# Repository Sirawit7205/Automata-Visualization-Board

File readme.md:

# CMOS Elementary Automata Visualization Board

This is an  open-source KiCad design files for a circuit that could generate and visualize [Elementary Automata](https://mathworld.wolfram.com/ElementaryCellularAutomaton.html) only by using common logic ICs. There are two versions available: Standard and Minimal. 

## Standard Version

Standard version is a large board of size 247x127mm (9.7x5in), suitable for putting in a frame. Featuring:

 - 26 Logic ICs in DIP package. (Okay, I have an ATMEGA328 here but it's here just to drive the display. Its firmware is available here as well.)
 - 1.44 inch TFT display with a display driver which can draws a complete picture of that elementary automata rule.
 - Fully visualized 65-bit shift register so you can see how the data flows.
 - Fully selectable 8-bit automata rule input.
 - An LSFR pseudo-random rules generator.
 - Status display.
 - Drawing speed adjustment.
 - All through hole design. Should be relatively easy to solder.

We are currently at Revision 3. Changelog is below:

**Revision 3 (July 2020)**
 - Fixed all of the issues found in rev 2.
 - BOMs consolidated to lessen the unique parts count.
 - New LFSR circuit, the rare CD4006 is no longer required.
 - Updated all footprints to the latest version.
 - Minor changes to the appearances of the PCB.

**Revision 2 (May 2020)**
 - Fixed Connector orientation for the display and the DIP switch.
 - Connected GND to mounting holes
 - Change of parts in the power section due to sourcing issue.
 
**Revision 1 (January 2020)**
 - Initial Design

## Minimal Version

Minimal Version is a smaller board of size 129x72mm (5x3in). It is suitable for carrying around to show off. Featuring:

 - 23 Logic ICs in SOT, SOIC, TSSOP, and TQFP packages.
 - 1.44 inch TFT display.
 - Fully selectable 8-bit automata rule input.
 - An LSFR pseudo-random rules generator.
 - Status display.
 - Drawing speed adjustment.
 - Very challenging SMD soldering practice kit.
 - The PCB should be much cheaper to produce. It's still a little bit too large to fit in 10x10cm requirements for many cheap PCB fabs though, I might try to squeeze it down later.

We are currently at Revision 3. Changelog is below:

**Revision 3 (July 2020)**
 - Fixed all of the issues found in smd rev 2.
 - BOMs consolidated to lessen the unique parts count.
 - New LFSR circuit, the rare CD4006 is no longer required.
 - Updated all footprints to the latest version.
 - Minor changes to the appearances of the PCB.

**Revision 2 (May 2020)**
 - Fixed all of the issues found in rev 1 of the Standard version.
 - Change of parts in the power section due to sourcing issue.
 
**Revision 1 (April 2020)**
 - Initial Design (Based on Standard version)

## What is provided
The goal of this repository is to enable you to build this on your own as easy as possible (although I originally plan to sell this as a kit as well). **I've included all of the schematics, gerbers, BOMs, and display driver firmware for you to use.** And this work is licensed under a [Creative Commons Attribution-NonCommercial 4.0 International License](http://creativecommons.org/licenses/by-nc/4.0/).

Unfortunately. I have to excluded the 3D models use to render the board in KiCAD because I don't know how each of them was licensed. They are all from GrabCad and you could search and download them by yourself.

**Note: Due to this, there might be a popup warning you about "3D model Search Path" in PCBNew. I honestly don't know how to fix this but it will not affect any KiCAD functionality.**

## Credits
 - DIP switch model by austfox: https://grabcad.com/library/dip-switches-1
 - 1.44inch LCD model by John: https://grabcad.com/library/1-44in-lcd-tft-1
 - Sliding switch model by Jonn: https://grabcad.com/library/selector-switch-assortment-1
 - Trimpot model by Markus Walter: https://grabcad.com/library/bourns-3362p-1-102lf
 - DIP ICs in socket models by Dirk Wouters: https://grabcad.com/library/ic-dip-packages-with-sockets-in-pitch-7-62mm-1
 - TO-220 package model by Egor Chugay: https://grabcad.com/library/to-220-transistor-package-1
 - DC Power Jack model by J. F. Gomez: https://grabcad.com/library/dc-power-jack-5-5mm-x-2-1mm-2-54mm-pitch-1
 - SMD 5032 Crystal 2-Pin model by Dirk Wouters: https://grabcad.com/library/smd-5032-crystal-2-pin-1
 - LED Bar Graph model by austfox: https://grabcad.com/library/led-bar-graph-2
 - 3306P1102, 3362P_1, NE555DR, OS102011MA1QN1, TO229P239X654X978-3P footprint symbols by SamacSys

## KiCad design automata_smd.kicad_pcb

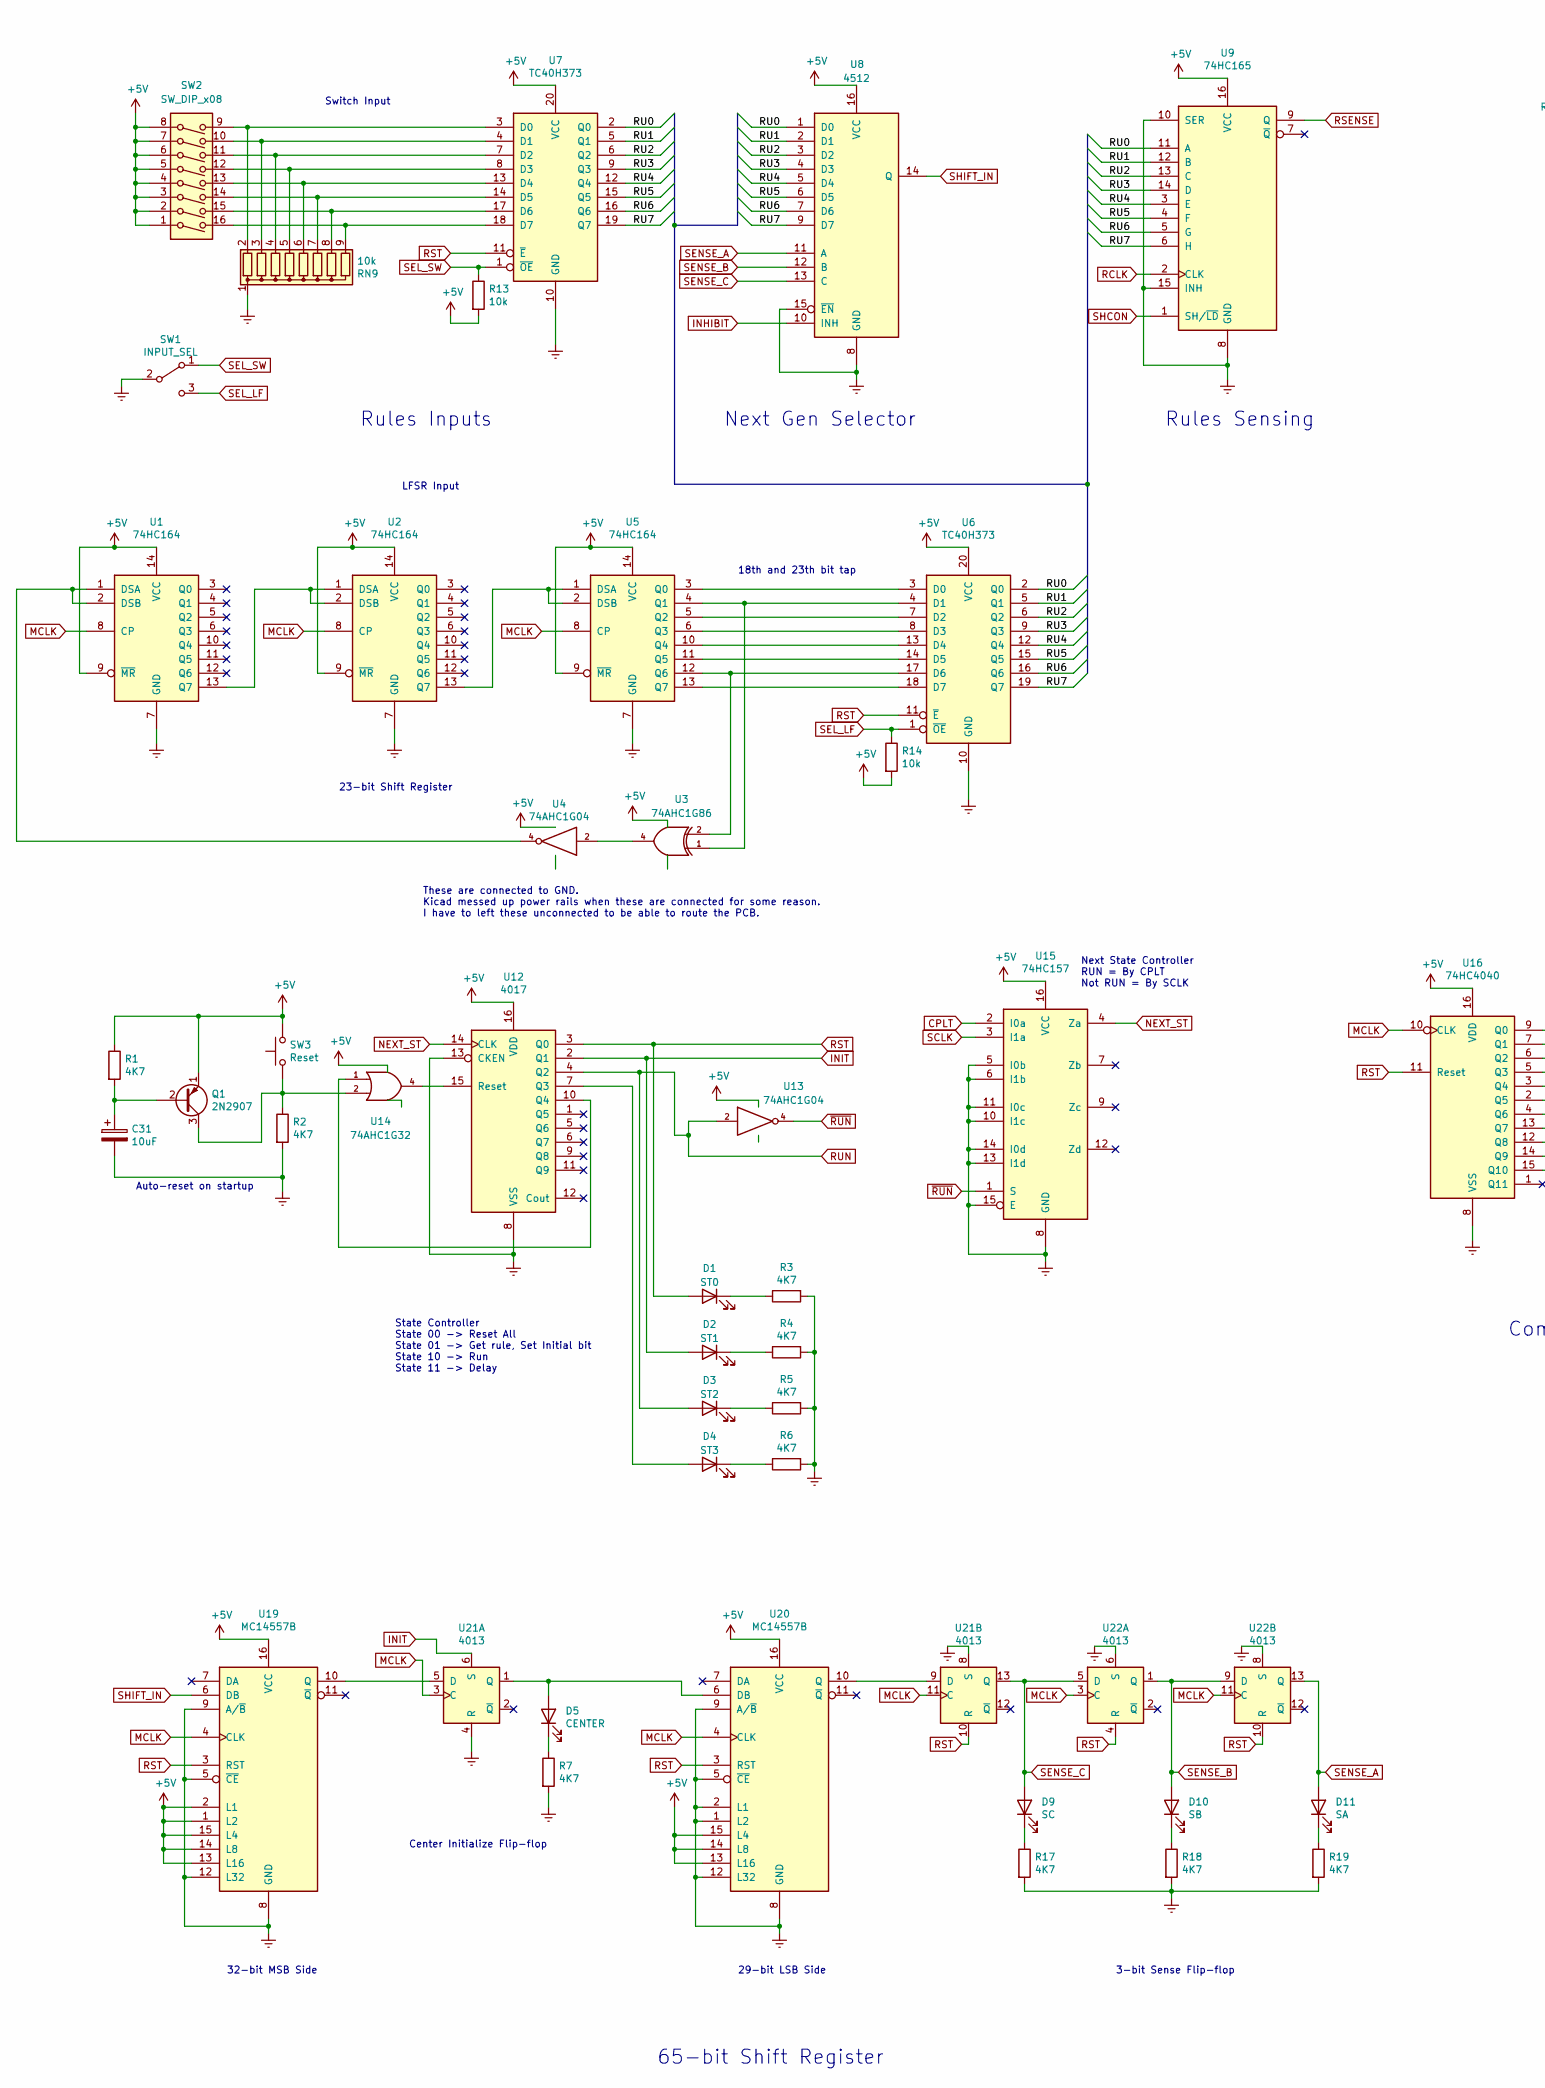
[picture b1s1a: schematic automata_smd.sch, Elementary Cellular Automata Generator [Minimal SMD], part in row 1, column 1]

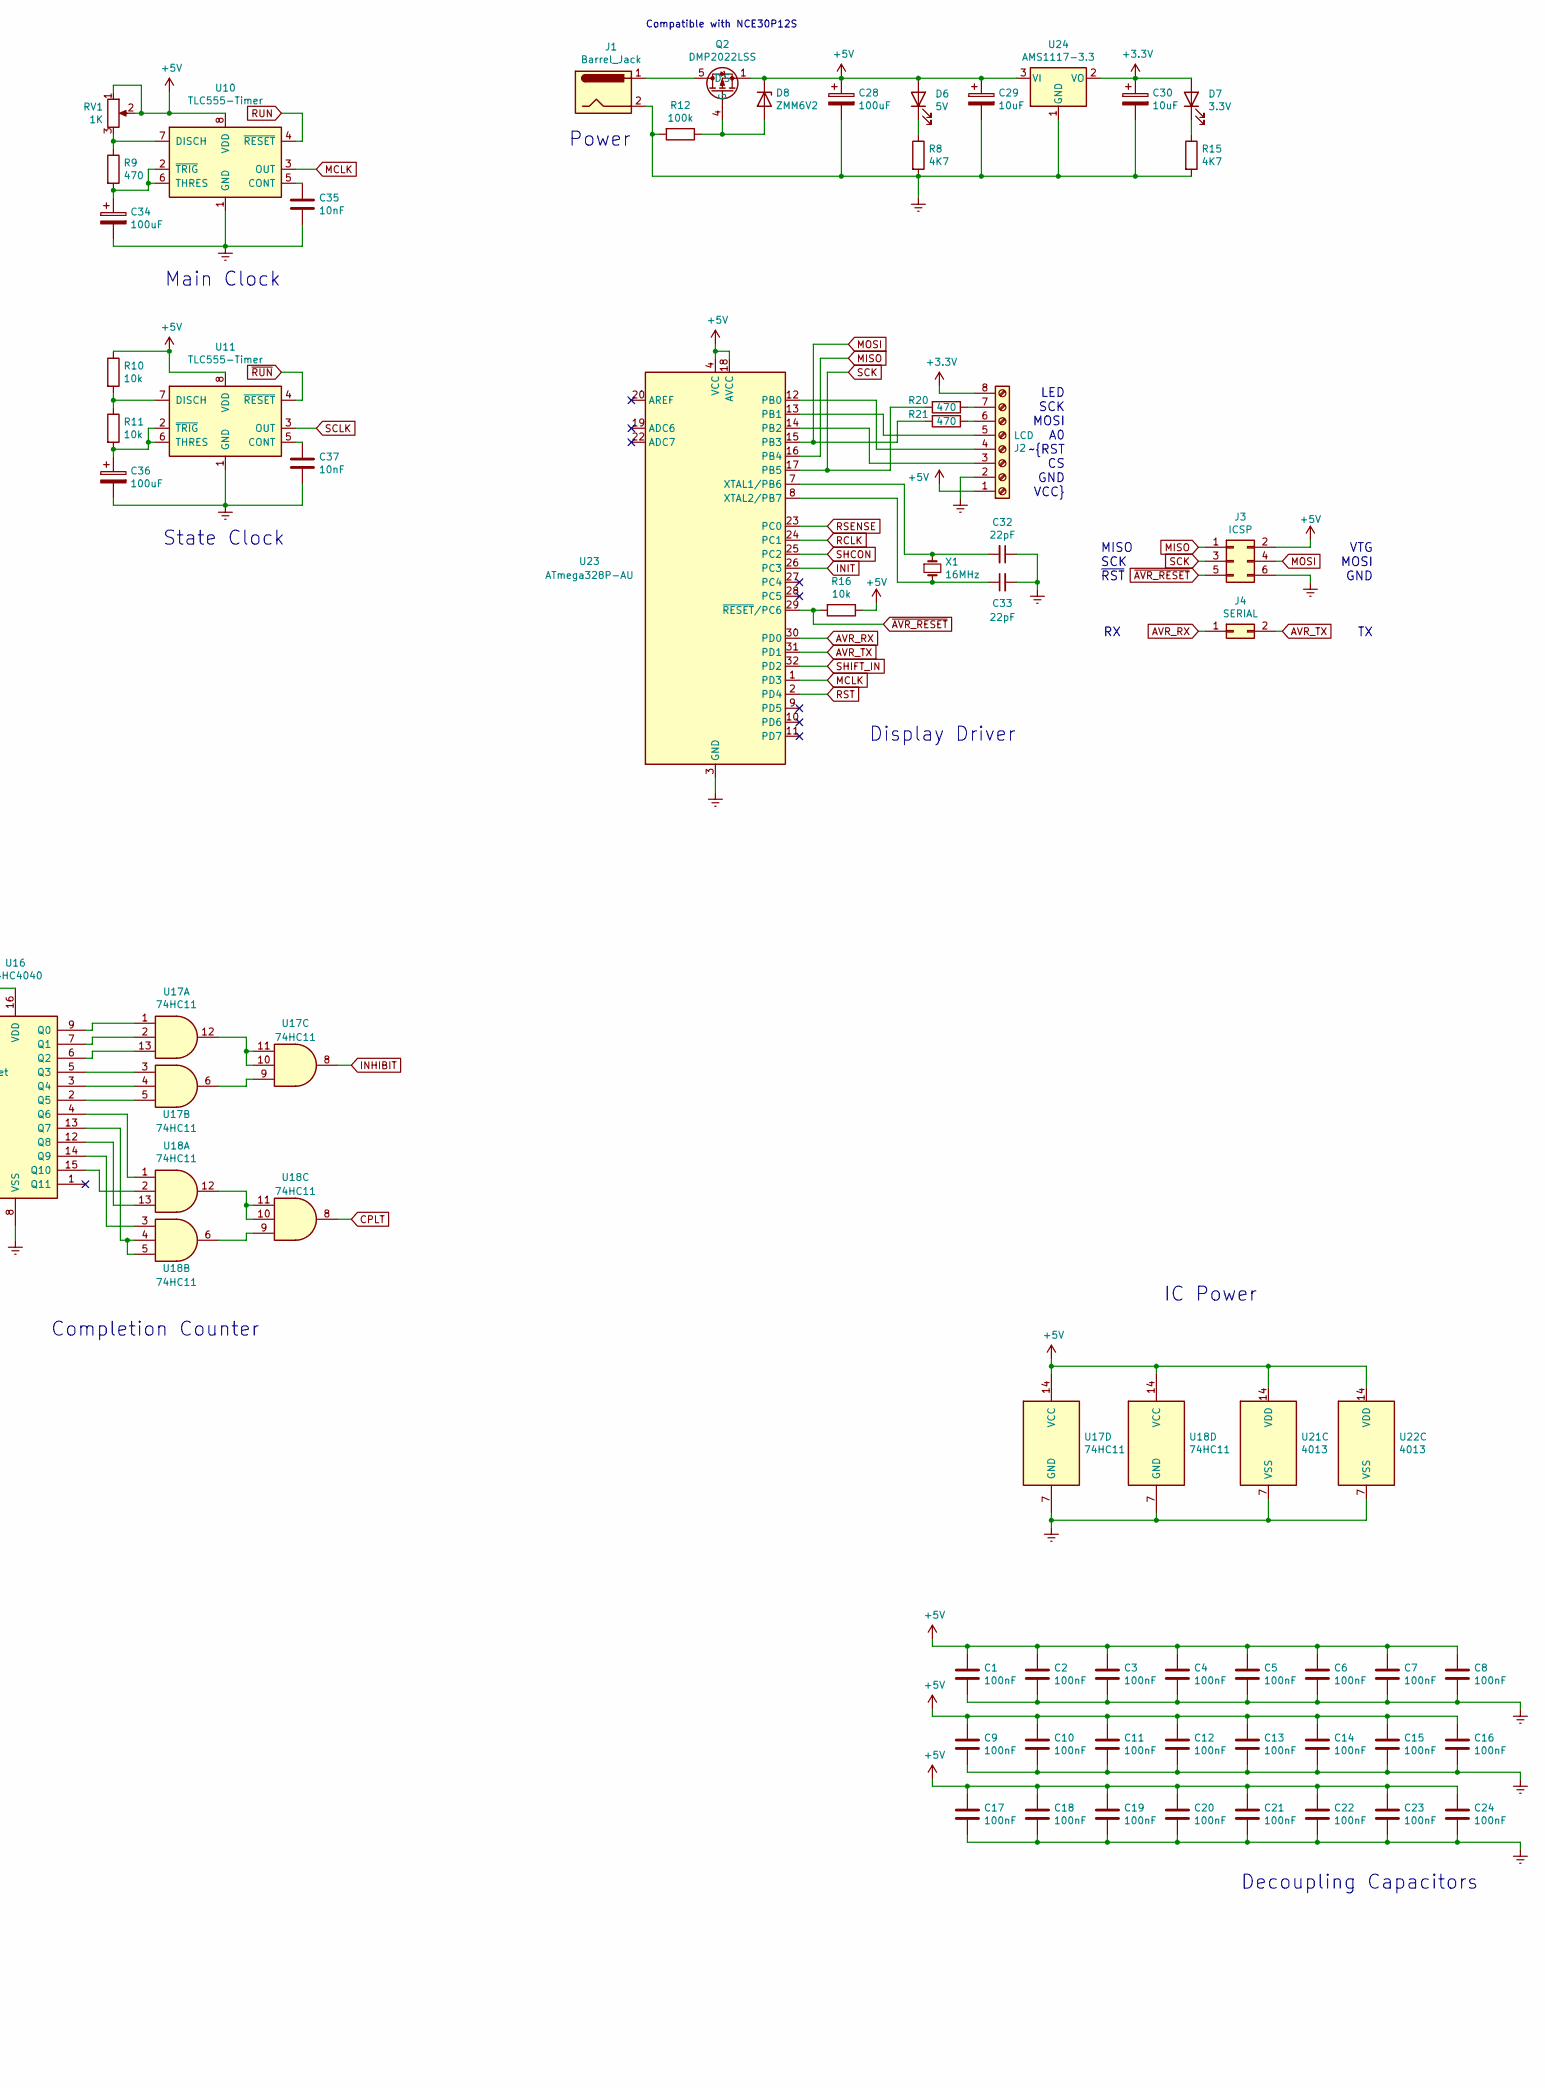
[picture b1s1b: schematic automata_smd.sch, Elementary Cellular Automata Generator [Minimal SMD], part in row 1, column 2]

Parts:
C1: 100nF; TSSOP-14_4.4x5mm_P0.65mm
C2, C3, C4, C5, C6, C7, C8, C9, C10, C11, C12, C13, C14, C15, C16, C17, C18, C19, C20, C21, C22, C23, C24: 100nF; C_0603_1608Metric
C28, C34, C36: 100uF; CP_Radial_D8.0mm_P2.50mm
C29, C30, C31: 10uF; CP_Radial_D5.0mm_P2.00mm
C32, C33: 22pF; C_0603_1608Metric
C35, C37: 10nF; C_0603_1608Metric
D1: ST0; LED_0603_1608Metric
D2: ST1; LED_0603_1608Metric
D3: ST2; LED_0603_1608Metric
D4: ST3; LED_0603_1608Metric
D5: CENTER; LED_0603_1608Metric
D6: 5V; LED_0603_1608Metric
D7: 3.3V; LED_0603_1608Metric
D8: ZMM6V2; D_MiniMELF
D9: SC; LED_0603_1608Metric
D10: SB; LED_0603_1608Metric
D11: SA; LED_0603_1608Metric
J1: Barrel_Jack; BarrelJack_Horizontal
J2: LCD; PinHeader_1x08_P2.54mm_Vertical
J3: ICSP; PinHeader_2x03_P2.54mm_Vertical
J4: SERIAL; PinHeader_2x01_P2.54mm_Vertical
Q1: 2N2907; SOT-23
Q2: DMP2022LSS; SO-8_3.9x4.9mm_P1.27mm
R1, R2, R3, R4, R5, R6, R7, R8, R15, R17, R18, R19: 4K7; R_0603_1608Metric
R9, R20, R21: 470; R_0603_1608Metric
R10, R11, R13, R14, R16: 10k; R_0603_1608Metric
R12: 100k; R_0603_1608Metric
RN9: 10k; R_Array_SIP9
RV1: 1K; 3362P_1
SW1: INPUT_SEL; OS102011MA1QN1
SW2: SW_DIP_x08; SW_DIP_SPSTx08_Slide_9.78x22.5mm_W7.62mm_P2.54mm
SW3: Reset; SW_PUSH_6mm
U1, U2, U5: 74HC164; TSSOP-14_4.4x5mm_P0.65mm
U3: 74AHC1G86; SOT-23-5
U4, U13: 74AHC1G04; SOT-23-5
U6, U7: TC40H373; TSSOP-20_4.4x6.5mm_P0.65mm
U8: 4512; TSSOP-16_4.4x5mm_P0.65mm
U9: 74HC165; TSSOP-16_4.4x5mm_P0.65mm
U10, U11: TLC555-Timer; SOIC-8_3.9x4.9mm_P1.27mm
U12: 4017; TSSOP-16_4.4x5mm_P0.65mm
U14: 74AHC1G32; SOT-23-5
U15: 74HC157; TSSOP-16_4.4x5mm_P0.65mm
U16: 74HC4040; TSSOP-16_4.4x5mm_P0.65mm
U17, U18: 74HC11; TSSOP-14_4.4x5mm_P0.65mm
U19, U20: MC14557B; SOIC-16W_7.5x10.3mm_P1.27mm
U21, U22: 4013; TSSOP-14_4.4x5mm_P0.65mm
U23: ATmega328P-AU; TQFP-32_7x7mm_P0.8mm
U24: AMS1117-3.3; SOT-223-3_TabPin2
X1: 16MHz; Crystal_SMD_5032-2Pin_5.0x3.2mm

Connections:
+3V3: C30.1, D7.2 (A), J2.8, U24.2 (VO)
/RU0: U6.2 (Q0), U7.2 (Q0), U8.1 (D0), U9.11 (A)
/RU1: U6.5 (Q1), U7.5 (Q1), U8.2 (D1), U9.12 (B)
/RU2: U6.6 (Q2), U7.6 (Q2), U8.3 (D2), U9.13 (C)
/RU3: U6.9 (Q3), U7.9 (Q3), U8.4 (D3), U9.14 (D)
/RU4: U6.12 (Q4), U7.12 (Q4), U8.5 (D4), U9.3 (E)
/RU5: U6.15 (Q5), U7.15 (Q5), U8.6 (D5), U9.4 (F)
/RU6: U6.16 (Q6), U7.16 (Q6), U8.7 (D6), U9.5 (G)
/RU7: U6.19 (Q7), U7.19 (Q7), U8.9 (D7), U9.6 (H)
AVR_RX: J4.1, U23.30 (PD0)
AVR_TX: J4.2, U23.31 (PD1)
CPLT: U15.2 (I0a), U18.8
INHIBIT: U8.10 (INH), U17.8
INIT: D2.2 (A), U12.2 (Q1), U21.6 (S), U23.26 (PC3)
MCLK: U1.8 (CP), U2.8 (CP), U5.8 (CP), U10.3 (OUT), U16.10 (CLK), U19.4 (CLK), U20.4 (CLK), U21.3 (C), U21.11 (C), U22.3 (C), U22.11 (C), U23.1 (PD3)
MISO: J3.1, U23.16 (PB4)
MOSI: J3.4, R21.2, U23.15 (PB3)
NEXT_ST: U12.14 (CLK), U15.4 (Za)
unnamed: C31.1, Q1.2 (B), R1.2
unnamed: C32.2, U23.7 (XTAL1/PB6), X1.1
unnamed: C33.1, U23.8 (XTAL2/PB7), X1.2
unnamed: C34.1, R9.2, U10.2 (~TRIG), U10.6 (THRES)
unnamed: C35.1, U10.5 (CONT)
unnamed: C36.1, R11.2, U11.2 (~TRIG), U11.6 (THRES)
unnamed: C37.1, U11.5 (CONT)
unnamed: D1.1 (K), R3.1
unnamed: D2.1 (K), R4.1
unnamed: D3.1 (K), R5.1
unnamed: D4.1 (K), R6.1
unnamed: D4.2 (A), U12.7 (Q3)
unnamed: D5.1 (K), R7.1
unnamed: D5.2 (A), U20.6 (DB), U21.1 (Q)
unnamed: D6.1 (K), R8.1
unnamed: D7.1 (K), R15.1
unnamed: D8.2 (A), Q2.4 (G), R12.1
unnamed: D9.1 (K), R17.1
unnamed: D10.1 (K), R18.1
unnamed: D11.1 (K), R19.1
unnamed: J1.1, Q2.5 (D), Q2.6 (D), Q2.7 (D), Q2.8 (D)
unnamed: J2.3, U23.14 (PB2)
unnamed: J2.4, U23.12 (PB0)
unnamed: J2.5, U23.13 (PB1)
unnamed: J2.6, R21.1
unnamed: J2.7, R20.1
unnamed: Q1.3 (C), R2.1, SW3.1, U14.2
unnamed: R9.1, RV1.3, U10.7 (DISCH)
unnamed: R10.2, R11.1, U11.7 (DISCH)
unnamed: RN9.2 (R1), SW2.9, U7.3 (D0)
unnamed: RN9.3 (R2), SW2.10, U7.4 (D1)
unnamed: RN9.4 (R3), SW2.11, U7.7 (D2)
unnamed: RN9.5 (R4), SW2.12, U7.8 (D3)
unnamed: RN9.6 (R5), SW2.13, U7.13 (D4)
unnamed: RN9.7 (R6), SW2.14, U7.14 (D5)
unnamed: RN9.8 (R7), SW2.15, U7.17 (D6)
unnamed: RN9.9 (R8), SW2.16, U7.18 (D7)
unnamed: U1.1 (DSA), U1.2 (DSB), U4.4
unnamed: U1.13 (Q7), U2.1 (DSA), U2.2 (DSB)
unnamed: U2.13 (Q7), U5.1 (DSA), U5.2 (DSB)
unnamed: U3.1, U5.4 (Q1), U6.4 (D1)
unnamed: U3.2, U5.12 (Q6), U6.17 (D6)
unnamed: U3.4, U4.2
unnamed: U5.3 (Q0), U6.3 (D0)
unnamed: U5.5 (Q2), U6.7 (D2)
unnamed: U5.6 (Q3), U6.8 (D3)
unnamed: U5.10 (Q4), U6.13 (D4)
unnamed: U5.11 (Q5), U6.14 (D5)
unnamed: U5.13 (Q7), U6.18 (D7)
unnamed: U12.10 (Q4), U14.1
unnamed: U12.15 (Reset), U14.4
unnamed: U16.2 (Q5), U17.5
unnamed: U16.3 (Q4), U17.4
unnamed: U16.4 (Q6), U18.1
unnamed: U16.5 (Q3), U17.3
unnamed: U16.6 (Q2), U17.13
unnamed: U16.7 (Q1), U17.2
unnamed: U16.9 (Q0), U17.1
unnamed: U16.12 (Q8), U18.13
unnamed: U16.13 (Q7), U18.4, U18.5
unnamed: U16.14 (Q9), U18.3
unnamed: U16.15 (Q10), U18.2
unnamed: U17.6, U17.9
unnamed: U17.10, U17.11, U17.12
unnamed: U18.6, U18.9
unnamed: U18.10, U18.11, U18.12
unnamed: U19.10 (Q), U21.5 (D)
unnamed: U20.10 (Q), U21.9 (D)
RCLK: U9.2 (CLK), U23.24 (PC1)
RSENSE: U9.9 (Q), U23.23 (PC0)
RST: D1.2 (A), U6.11 (~E), U7.11 (~E), U12.3 (Q0), U16.11 (Reset), U19.3 (RST), U20.3 (RST), U21.10 (R), U22.4 (R), U22.10 (R), U23.2 (PD4)
RUN: D3.2 (A), U10.4 (~RESET), U12.4 (Q2), U13.2
SCK: J3.3, R20.2, U23.17 (PB5)
SCLK: U11.3 (OUT), U15.3 (I1a)
SEL_LF: R14.1, SW1.3 (C), U6.1 (~OE)
SEL_SW: R13.1, SW1.1 (A), U7.1 (~OE)
SENSE_A: D11.2 (A), U8.11 (A), U22.13 (Q)
SENSE_B: D10.2 (A), U8.12 (B), U22.1 (Q), U22.9 (D)
SENSE_C: D9.2 (A), U8.13 (C), U21.13 (Q), U22.5 (D)
SHCON: U9.1 (SH/~LD), U23.25 (PC2)
SHIFT_IN: U8.14 (Q), U19.6 (DB), U23.32 (PD2)
~AVR_RESET: J3.5, R16.2, U23.29 (~RESET~/PC6)
~RUN: U11.4 (~RESET), U13.4, U15.1 (S)

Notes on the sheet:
Switch Input
Rules Inputs
Next Gen Selector
Completion Counter
LED SCK MOSI A0 ~RST CS GND VCC
Power
Display Driver
Rules Sensing
State Controller State 00 -> Reset All State 01 -> Get rule, Set Initial bit State 10 -> Run State 11 -> Delay
Auto-reset on startup
State Clock
Next State Controller RUN = By CPLT Not RUN = By SCLK
65-bit Shift Register
Center Initialize Flip-flop
Main Clock
Decoupling Capacitors
IC Power
32-bit MSB Side
29-bit LSB Side
3-bit Sense Flip-flop
MISO SCK ~RST
VTG MOSI GND
Compatible with NCE30P12S
LFSR Input
23-bit Shift Register
18th and 23th bit tap
These are connected to GND. Kicad messed up power rails when these are connected for some reason. I have to left these unconnected to be able to route the PCB.

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
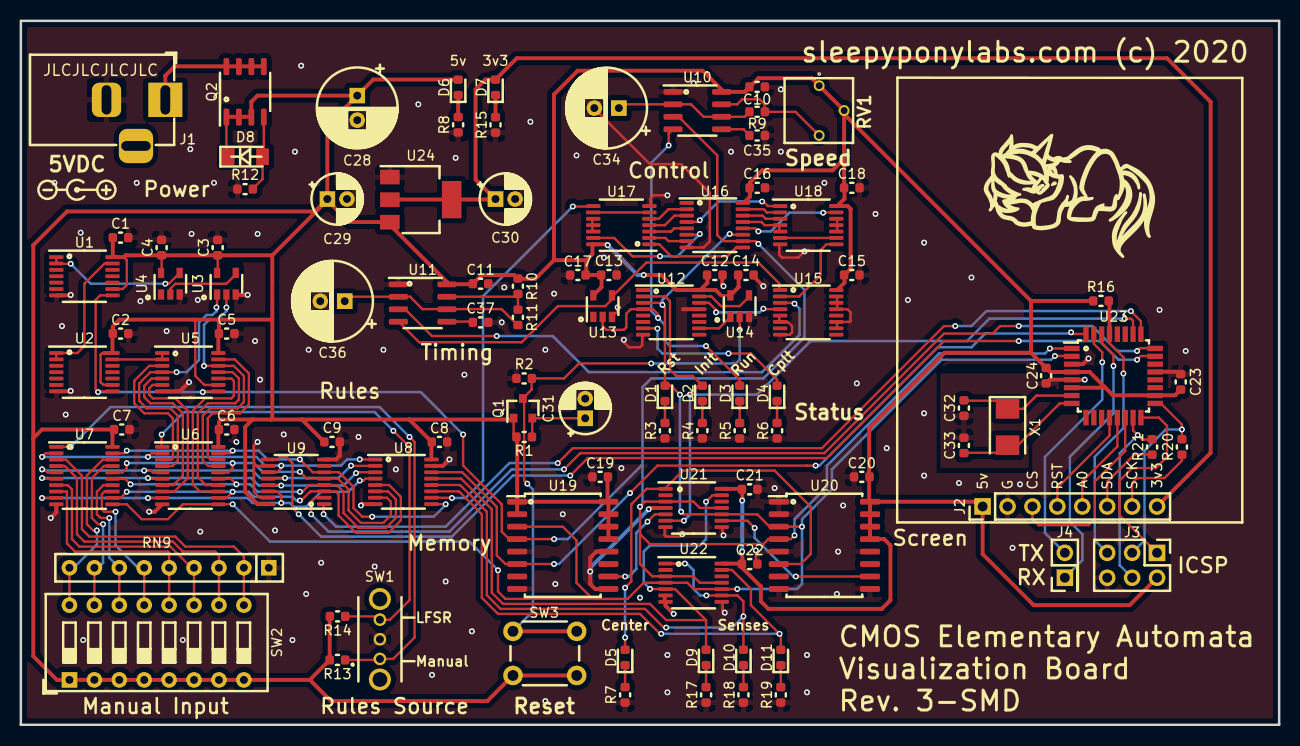
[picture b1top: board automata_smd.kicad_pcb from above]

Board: 2 copper layers, 128.3 x 71.8 mm, 104 parts (0 on the bottom side), 103 nets.

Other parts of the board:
G1: LOGO; sleepylogo_20mm
REF1: Symbol_Barrel_Polarity

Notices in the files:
automata.kicad_pcb:
sleepyponylabs.com (c) 2020
